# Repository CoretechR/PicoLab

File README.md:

# Pico.Lab - Web-GUI Embedded Multitool

## Overview

Pico.Lab is an open-source embedded bring-up tool built around the Raspberry Pi RP2350 microcontroller. It offers an easy-to-use, window-based web user interface directly served from on-device flash over a virtual USB Ethernet link. No host software or drivers are required - just plug it in and open your browser. The interface provides a 4-channel scope, an 8-channel logic analyzer, and an adjustable power supply with real-time monitoring. It also integrates GPIO control, a data logger, and bus masters for UART, SPI, and I2C communication.

## Features

*   **Easy to use**: A fast and intuitive window-based user interface lets you control all the integrated tools easily. It supports multitasking across its tools, windows-resizing and customization. For automation you can use the integrated CLI via the virtual COM port.
*   **No extra software or hardware needed**: The entire graphical interface is hosted on device using a lightweight web server. No WebUSB needed - It works seamlessly in any browser on any modern operating system. At only 200 KB in size, the interface fits comfortably in the Pico's RAM and loads in a fraction of a second.
*   **Integrated tools**: The firmware enables the Raspberry Pi Pico to become a multi-functional instrument for analog and digital debugging. The following tools are implemented so far:
    *   **Oscilloscope**: 4-channel analog capture with configurable timebase, voltage scaling, trigger settings, and continuous/single-shot modes. Utilizes overclocked ADC (192MHz) and DMA for high-speed continuous streaming for a bandwidth of around 400 kHz.
    *   **GPIO Control**: Directly read, write, and configure the 8 GPIO pins. Supports input/output modes, Pull-up configuration, and PWM control.
    *   **Data Logger**: Long-term, slow-rate sampling of both analog and digital pins with direct `.csv` export functionality.
    *   **Logic Analyzer**: 8-channel digital capture (D0–D7) capable of capturing at up to 100 MS/s. Features adjustable timebases, edge triggering, and Run-Length Encoding (RLE) compression for high-speed transmission. Integrated decoders for UART, I2C and SPI.
    *   **UART Terminal**: Serial bridge for interacting with target devices. Includes baud rate configuration, CR/LF ending controls, and live TX/RX logging.
    *   **Power Supply Controller**: Real-time control and monitoring of adjustable voltage/current rails (5V, 3.3V, and a fully adjustable output). Live telemetry graphing for current draw and voltage levels. Only available when using the Pico.Lab board.
    *   **I2C & SPI Masters**: Dedicated bus tools to scan for I2C devices, configure bus baud rates, and execute raw read/write transactions.

## Software

Pico.Lab is built entirely on native, lightweight frameworks to maximize the RP2350's performance.

*   **Firmware Backend (C)**:
    *   Built on the **Raspberry Pi Pico SDK**.
    *   **TinyUSB**: Provides USB CDC (Serial CLI) and RNDIS/ECM (Virtual Ethernet).
    *   **lwIP**: Handles TCP/IP, DHCP (assigning an IP to your PC), DNS (resolving `pico.lab`), and the embedded HTTP server.
    *   **Dual-Core Processing**: Core 0 handles networking, USB, and UI serving. Core 1 is dedicated entirely to high-frequency ADC/DMA sampling and logic capturing.
*   **Web Frontend (HTML/JS/CSS)**:
    *   Zero-dependency Vanilla JavaScript UI. Runs fully offline.
    *   **WinBox.js**: Used for the robust, draggable, desktop-like window manager.
    *   **Server-Sent Events (SSE)**: Pushes high-speed live telemetry data from the Pico to the browser over TCP.

## Hardware

Pico.Lab is designed to run best on the custom Pico.Lab board, but is fully compatible with standard Raspberry Pi Pico (RP2040) and Raspberry Pi Pico 2 (RP2350) boards out of the box. So if you have a Pico lying around, give the .uf2 files a try!

The Pico.Lab board adds the following features:
* Support for logic voltages from 1.65V to 5.5V
* Adjustable power rail (1-5V)
* 4x Analog Channels with 12V input range and op-amp buffer
* 8x Digital Inputs/Outputs with configurable pull-ups
* Current measurement for 5V, 3.3V, and adjustable rail
* Dedicated SPI, I2C and UART pins
* Protection against ESD, over-voltage, over-current, reverse current

## Current State of this Project

My main goal for this project was to be an easy-to-use toolkit for simple debugging applications. You want to know why an I2C sensor does not respond, what current your Wifi module is drawing or why a servo does not move? Just plug your hardware in and start debugging without checking a manual first. But since this is running on a 1$ microcontroller over a USB 1.1 link, don't expect the performance of professional instruments. The Pico will do significantly worse than any dedicated scope or logic analyzer. However, with the existing hardware there is still room for improvements, for example:
* [ ] Save/Restore tool configurations
* [ ] JTAG support
* [ ] a servo tester app

## Getting Started

### Flashing the firmware
1. Download the corresponding .uf2 file for your Rp2040 or RP2350. 
2. Put the device into BOOTSEL-Mode and drop the .uf2-File into its volume.

### Connecting to Pico.Lab
1. Connect the Pico.Lab board to your computer via USB.
2. The board will mount as a virtual network adapter. It automatically acts as a DHCP server.
3. Open your web browser and navigate to:
   * **http://pico.lab**
   * *(Alternatively, http://192.168.7.1 if your OS doesn't support local DNS).*
### Serial CLI
If you prefer a command-line interface, Pico.Lab also acts as a standard USB Serial (CDC) device. Connect via your favorite serial terminal (e.g., PuTTY) at 115200 baud.
Type `help` to see a list of commands (e.g., `gpio`, `adc`, `power`, `i2c`, `spi`, `sys`).

## Building from Source

### Prerequisites
* [Raspberry Pi Pico SDK](https://github.com/raspberrypi/pico-sdk)
* CMake & Ninja/Make
* GCC ARM Embedded Toolchain

### Build Instructions
```bash
git clone https://github.com/CoretechR/picolab.git
cd picolab
mkdir build && cd build
cmake ..
make -j$(nproc)
```
Select your type of Raspberry Pi Pico board in the Pico SDK. For the Pico.Lab board, set the PICOLAB_HW_CUSTOM_BOARD define in board_config.h. You can also use this file to modify the pins for GPIO, SPI, I2C and UART.

Flash the resulting `.uf2` file to your board by holding the `BOOTSEL` button while plugging it in, then drag-and-drop the file to the `RPI-RP2` drive.

## Disclosure about AI Usage

While I remain pessimistic about the impact of AI on humanity, there is no putting it back in the box. For this project, I tried to embrace it and used it heavily to generate the firmware, web frontend and parts of the documentation. I wanted to see what I could achieve in the same amount of time that I normally put into my hobby projects. All art, design and architecture were conceived by me. 

## License

This project is licensed under the **GPL-3.0 License** - see the [LICENSE](LICENSE) file for details.
Copyright © 2026 Maximilian Kern.

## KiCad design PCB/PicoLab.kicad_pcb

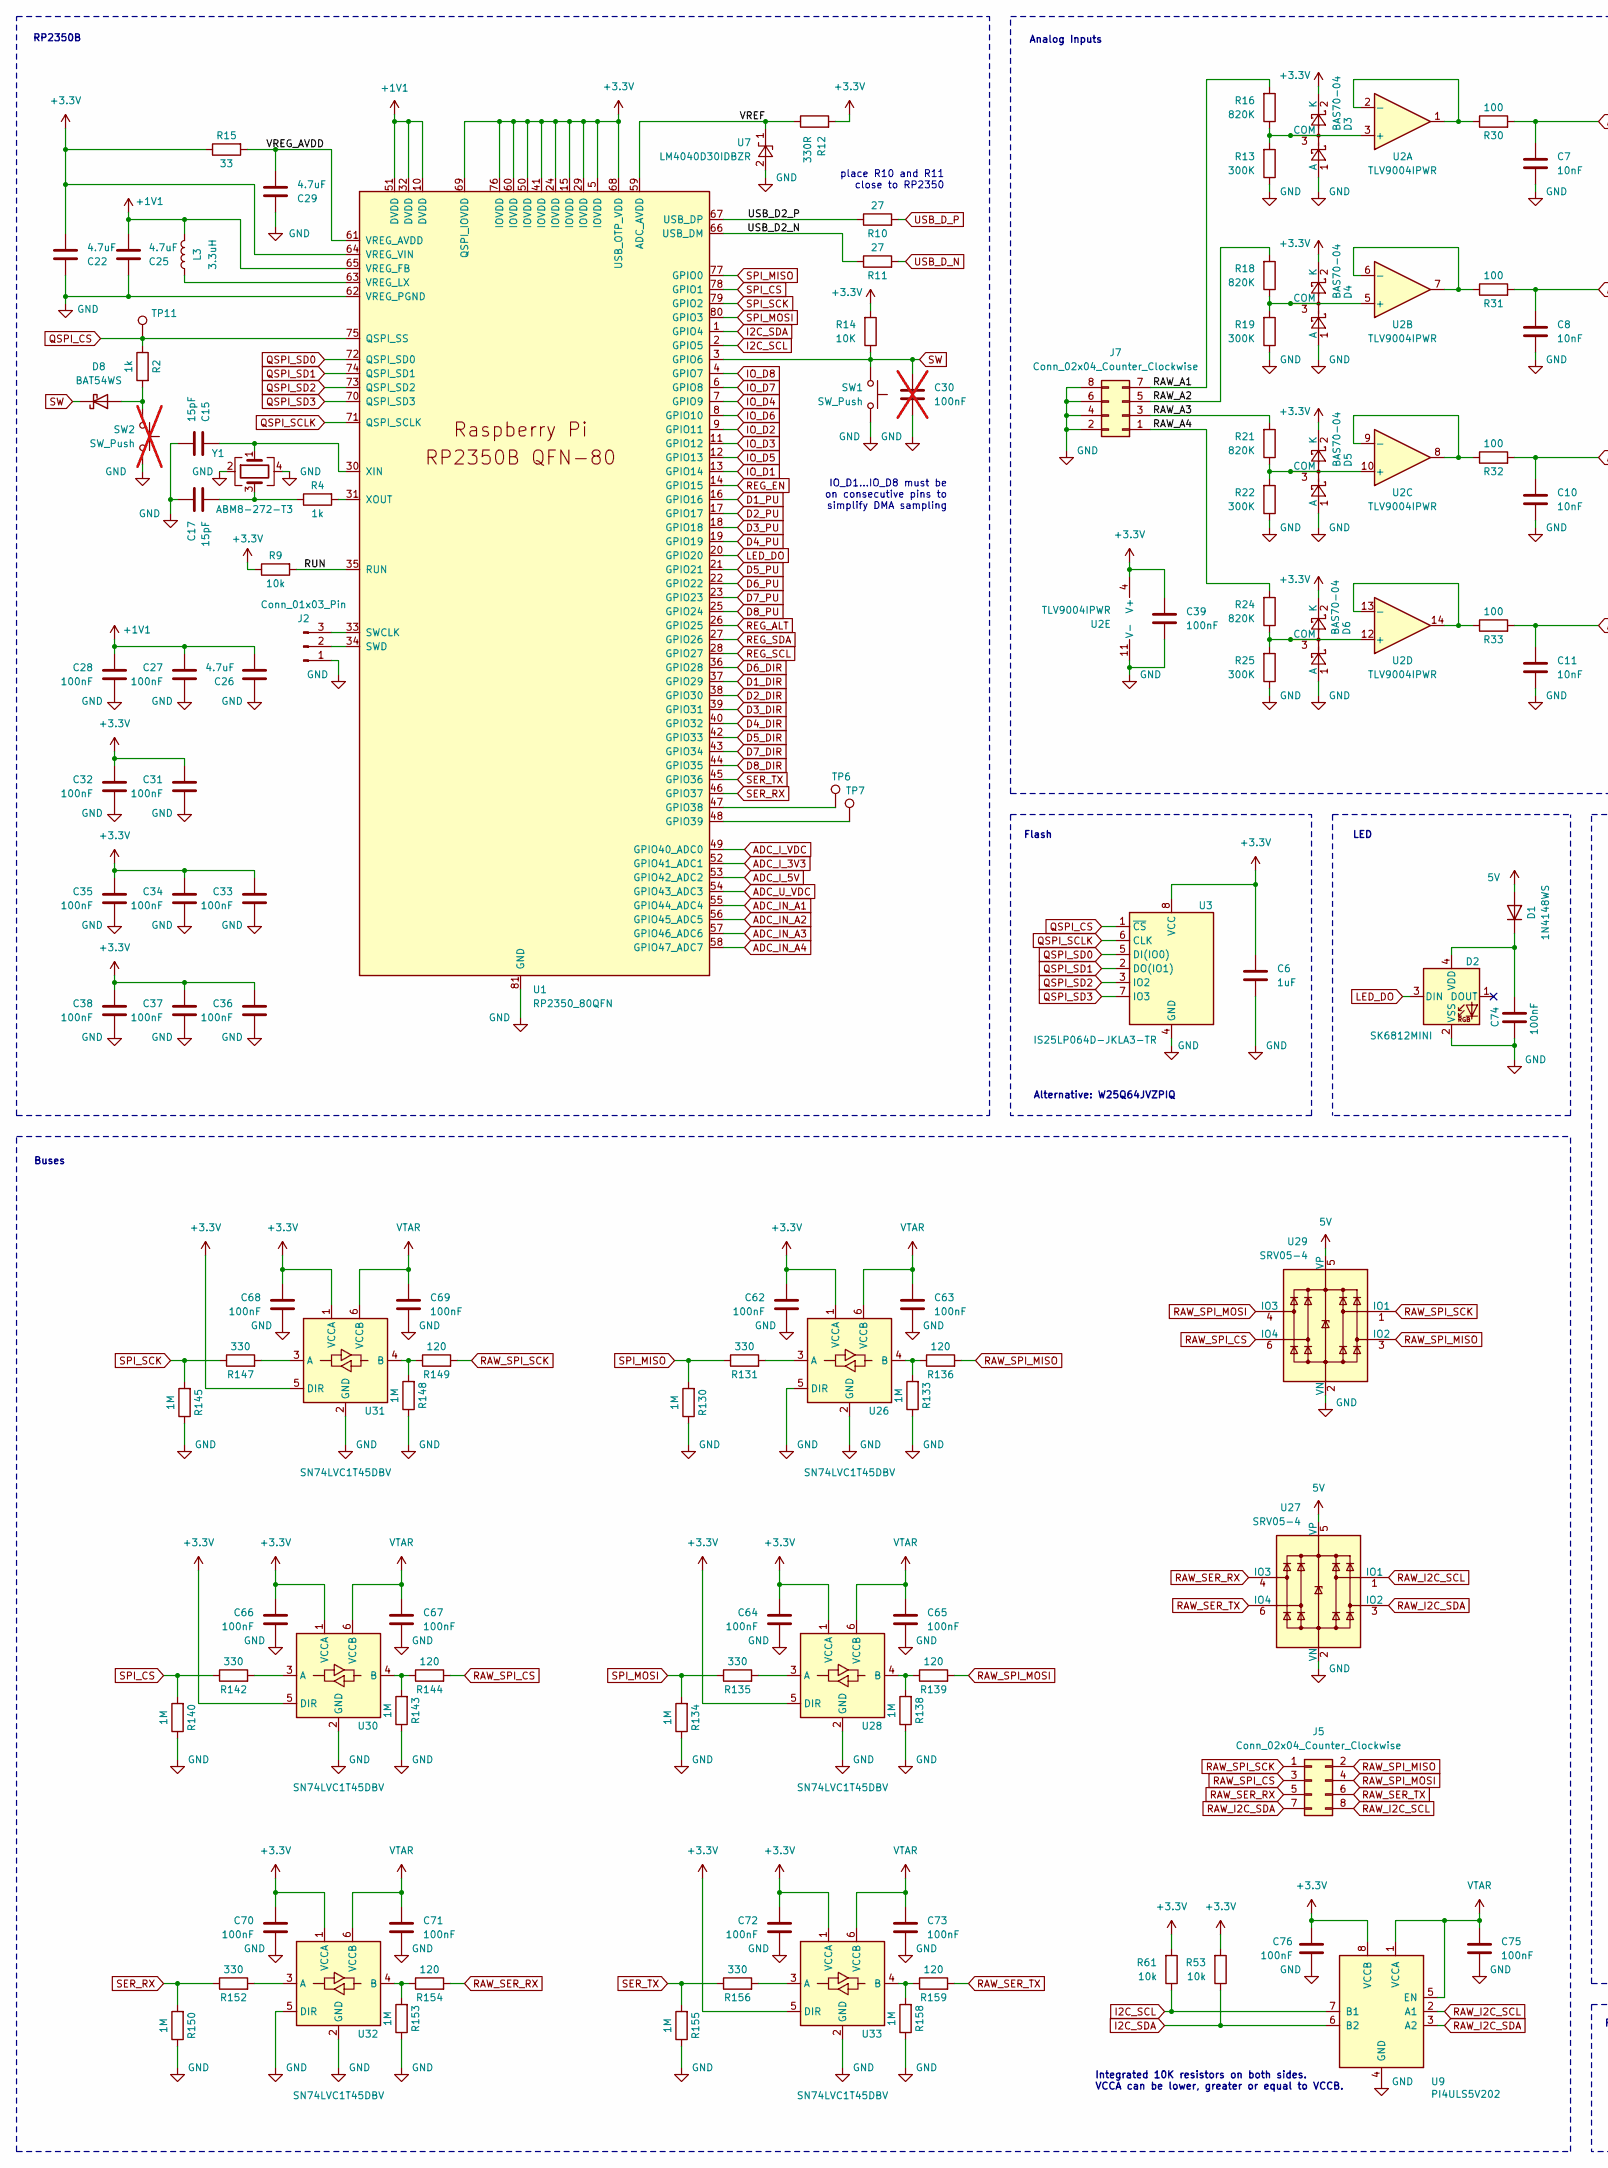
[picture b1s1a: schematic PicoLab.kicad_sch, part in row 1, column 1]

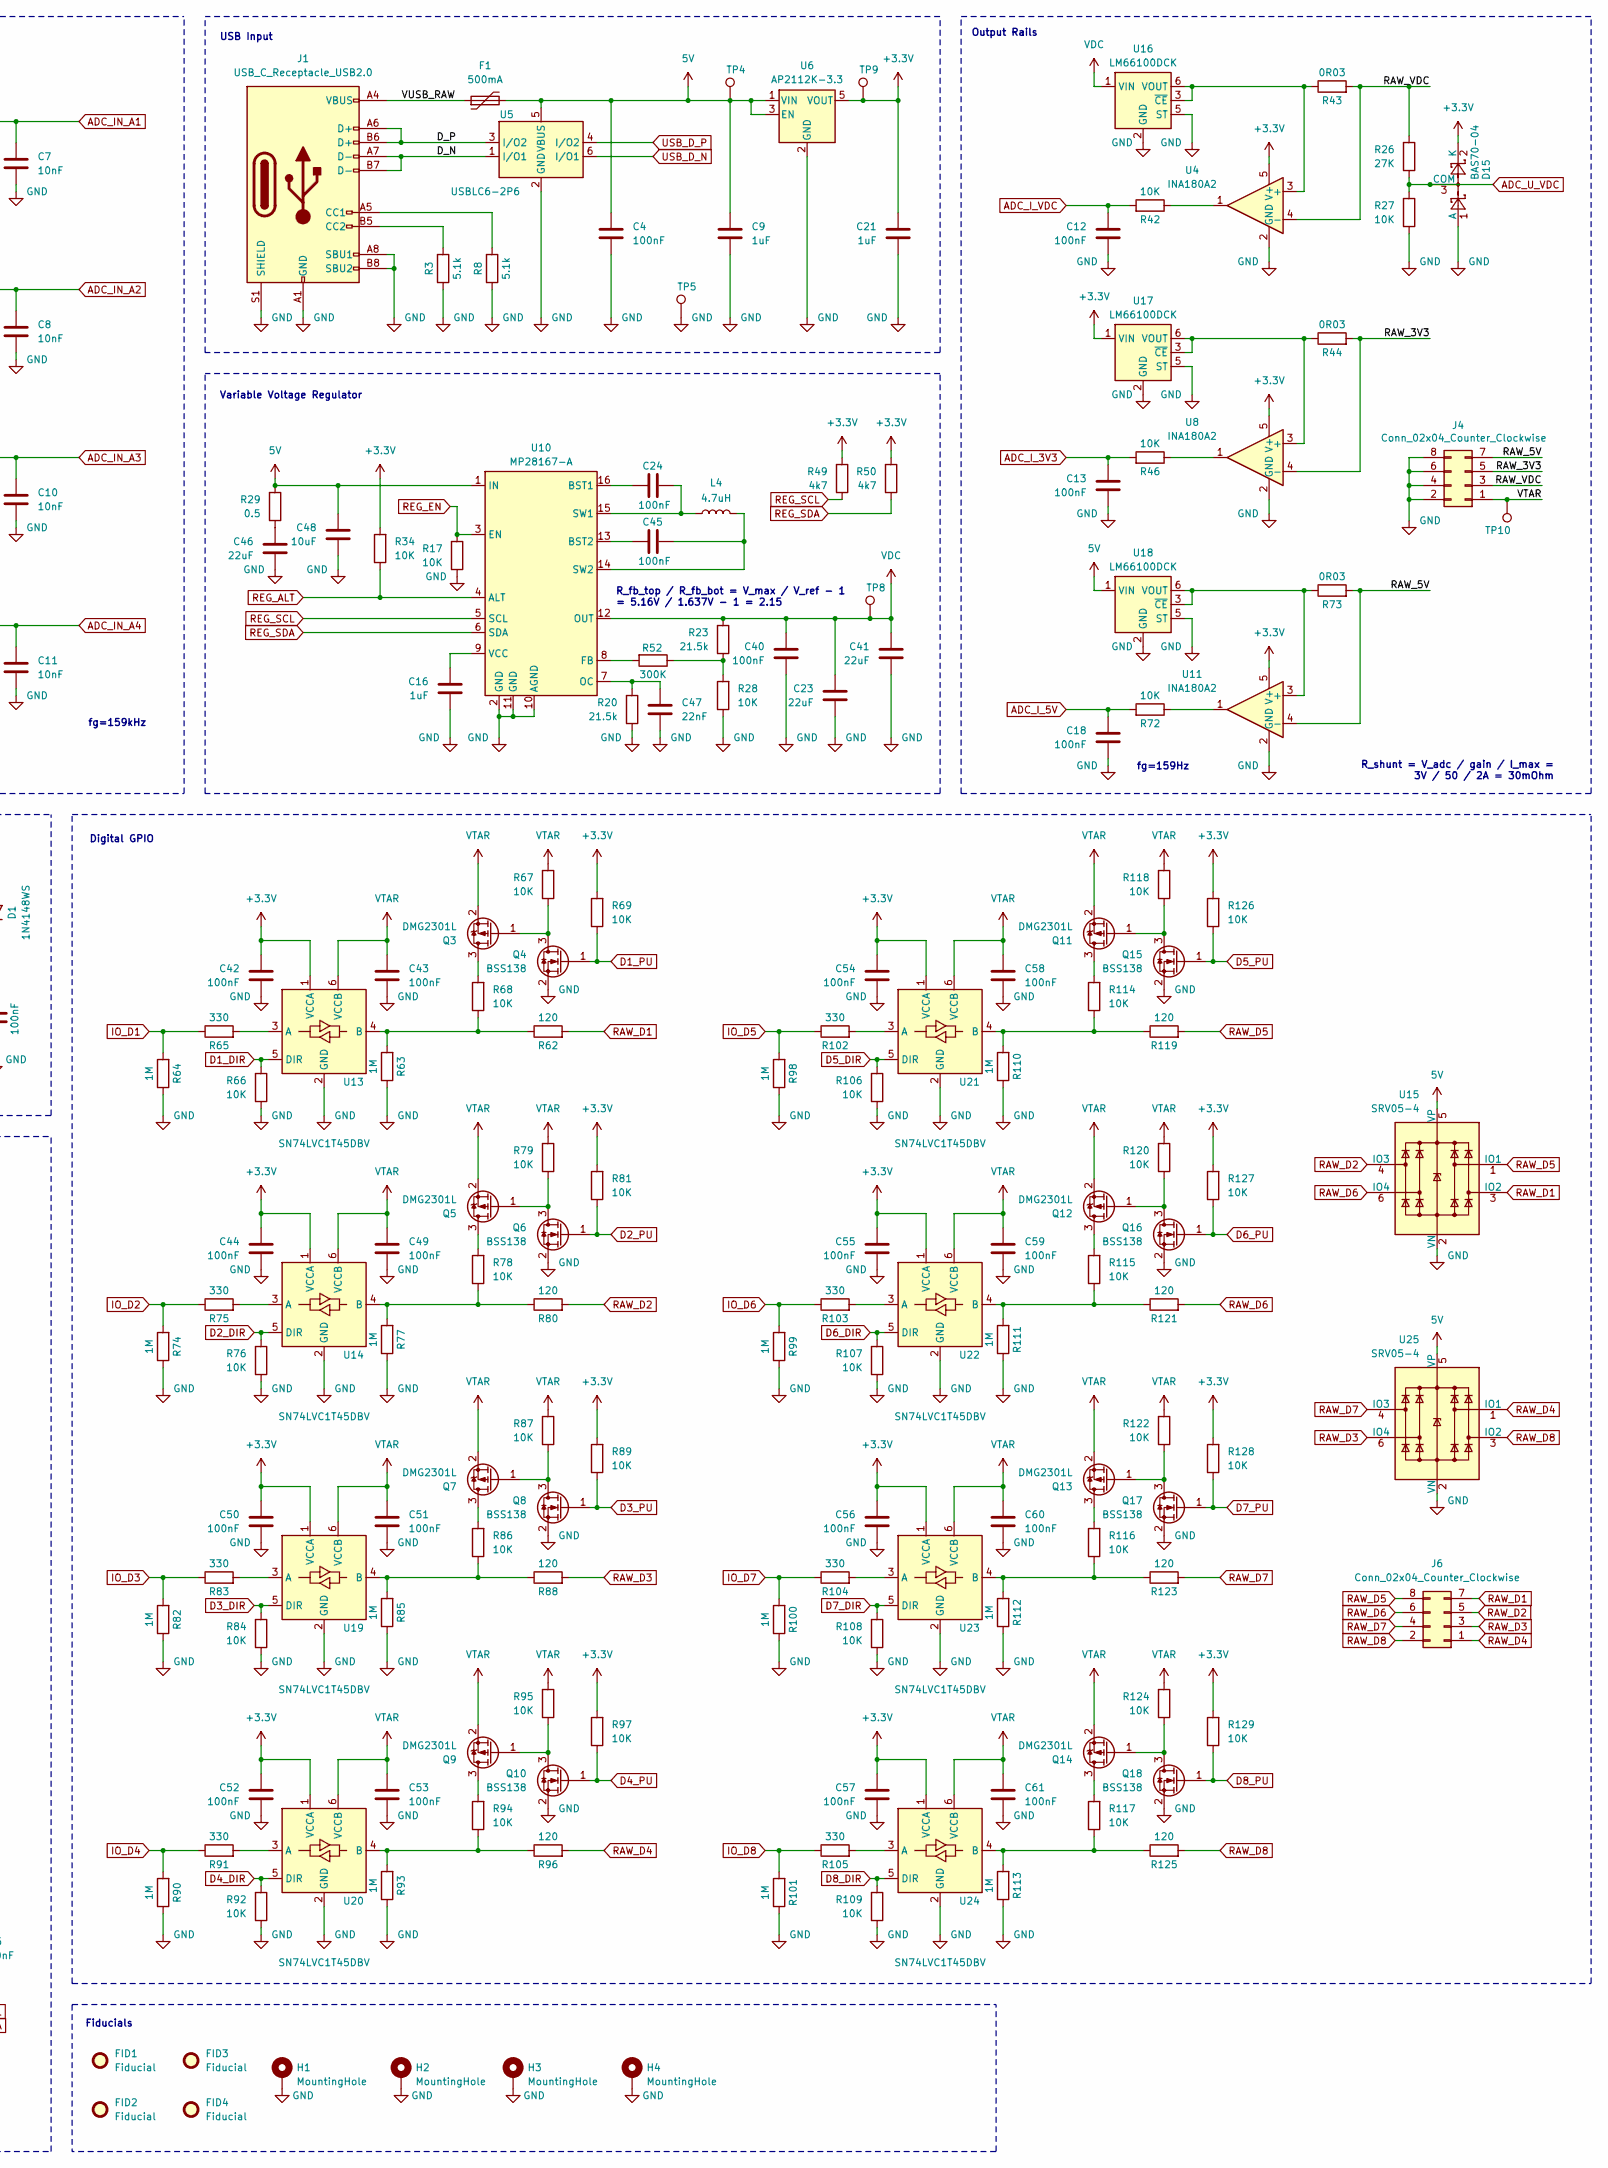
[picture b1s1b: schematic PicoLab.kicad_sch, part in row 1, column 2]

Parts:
C4, C12, C13, C18, C24, C27, C28, C31, C32, C33, C34, C35, C36, C37, C38, C39, C40, C42, C43, C44, C45, C49, C50, C51, C52, C53, C54, C55, C56, C57, C58, C59, C60, C61, C62, C63, C64, C65, C66, C67, C68, C69, C70, C71, C72, C73, C74, C75, C76: 100nF; C_0603_1608Metric; LCSC C1591
C6, C9, C16, C21: 1uF; C_0603_1608Metric; LCSC C15849
C7, C8, C10, C11: 10nF; C_0603_1608Metric
C15, C17: 15pF; C_0603_1608Metric; LCSC C107037
C22, C25, C26, C29: 4.7uF; C_0603_1608Metric; LCSC C1705
C23, C41: 22uF; C_1206_3216Metric; LCSC C91604
C30: 100nF; C_0603_1608Metric; LCSC C1591; not fitted
C46: 22uF; C_1206_3216Metric
C47: 22nF; C_0603_1608Metric; LCSC C106222
C48: 10uF; C_0805_2012Metric
D1: 1N4148WS; D_SOD-323; LCSC C118873
D2: SK6812MINI; LED_SK6812MINI_PLCC4_3.5x3.5mm_P1.75mm; LCSC C2886570
D3, D4, D5, D6: BAS70-04; SOT-23; LCSC C54194934
D8: BAT54WS; D_SOD-323; LCSC C124205
D15: BAS70-04; SOT-23
F1: 500mA; Fuse_1206_3216Metric_Pad1.42x1.75mm_HandSolder; LCSC C220146
FID1, FID2, FID3, FID4: Fiducial; Fiducial_1mm_Mask2mm
H1, H2, H3, H4: MountingHole; MountingHole_3.2mm_M3_Pad_Via
J1: USB_C_Receptacle_USB2.0; USB_C_Receptacle_HRO_TYPE-C-31-M-12; LCSC C2982555
J2: Conn_01x03_Pin; JST_SH_SM03B-SRSS-TB_1x03-1MP_P1.00mm_Horizontal; LCSC C160403
J4, J5, J6, J7: Conn_02x04_Counter_Clockwise; 10129382-908003BLF; LCSC C6970143
L3: 3.3uH; L_pol_2016; LCSC C42411119
L4: 4.7uH; L_1008_2520Metric; LCSC C668313
Q3, Q5, Q7, Q9, Q11, Q12, Q13, Q14: DMG2301L; SOT-23; LCSC C7472914
Q4, Q6, Q8, Q10, Q15, Q16, Q17, Q18: BSS138; SOT-23; LCSC C52895
R2, R4: 1k; R_0603_1608Metric; LCSC C22548
R3, R8: 5.1k; R_0603_1608Metric; LCSC C105580
R9, R53, R61: 10k; R_0603_1608Metric; LCSC C98220
R10, R11: 27; R_0603_1608Metric; LCSC C137753
R12: 330R; R_0603_1608Metric; LCSC C105881
R13, R19, R22, R25: 300K; R_0603_1608Metric
R14, R17, R27, R28, R34, R42, R46, R66, R67, R68, R69, R72, R76, R78, R79, R81, R84, R86, R87, R89, R92, R94, R95, R97, R106, R107, R108, R109, R114, R115, R116, R117, R118, R120, R122, R124, R126, R127, R128, R129: 10K; R_0603_1608Metric; LCSC C98220
R15: 33; R_0603_1608Metric
R16, R18, R21, R24: 820K; R_0603_1608Metric
R20, R23: 21.5k; R_0603_1608Metric
R26: 27K; R_0603_1608Metric
R29: 0.5; R_0603_1608Metric
R30, R31, R32, R33: 100; R_0603_1608Metric; LCSC C125923
R43, R44, R73: 0R03; R_0603_1608Metric; LCSC C422943
R49, R50: 4k7; R_0603_1608Metric; LCSC C99782
R52: 300K; R_0603_1608Metric; LCSC C116699
R62, R80, R88, R96, R119, R121, R123, R125, R136, R139, R144, R149, R154, R159: 120; R_0603_1608Metric; LCSC C125925
R63, R64, R74, R77, R82, R85, R90, R93, R98, R99, R100, R101, R110, R111, R112, R113, R130, R133, R134, R138, R140, R143, R145, R148, R150, R153, R155, R158: 1M; R_0603_1608Metric; LCSC C217860
R65, R75, R83, R91, R102, R103, R104, R105, R131, R135, R142, R147, R152, R156: 330; R_0603_1608Metric
SW1: SW_Push; Panasonic_EVQPUM_EVQPUD; LCSC C388642
SW2: SW_Push; SW_SPST_EVQP2_ShortPushTravel_H2.1mm; LCSC C2915174; not fitted
TP4, TP5, TP6, TP7, TP8, TP9, TP10, TP11: TestPoint; TestPoint_Pad_D1.5mm
U1: RP2350_80QFN; QFN-80-1EP_10x10mm_P0.4mm_EP3.4x3.4mm
U2: TLV9004IPWR; TSSOP-14_4.4x5mm_P0.65mm; LCSC C2058050
U3: IS25LP064D-JKLA3-TR; WSON-8-1EP_6x5mm_P1.27mm_EP3.4x4.3mm; LCSC C27531352
U4, U8, U11: INA180A2; SOT-23-5; LCSC C192764
U5: USBLC6-2P6; SOT-666; LCSC C2827693
U6: AP2112K-3.3; SOT-23-5; LCSC C51118
U7: LM4040D30IDBZR; SOT-23; LCSC C130178
U9: PI4ULS5V202; MSOP-8_3x3mm_P0.65mm; LCSC C481697
U10: MP28167-A; QFN-16_3x3mm_P0.5mm_MPS
U13, U14, U19, U20, U21, U22, U23, U24, U26, U28, U30, U31, U32, U33: SN74LVC1T45DBV; SOT-23-6; LCSC C7843
U15, U25, U27, U29: SRV05-4; SOT-23-6; LCSC C558418
U16, U17, U18: LM66100DCK; SOT-363_SC-70-6; LCSC C2869734
Y1: ABM8-272-T3; Crystal_SMD_Abracon_ABM8G-4Pin_3.2x2.5mm; LCSC C20625731

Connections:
5V: C4.1, C9.1, C48.1, D1.2 (A), F1.2, R29.2, TP4.1 (1_1), U5.5 (VBUS), U6.1 (VIN), U6.3 (EN), U10.1 (IN), U15.5 (VP), U18.1 (VIN), U25.5 (VP), U27.5 (VP), U29.5 (VP)
+1V1: C25.2, C26.2, C27.1, C28.1, L3.1, U1.10 (DVDD), U1.32 (DVDD), U1.51 (DVDD), U1.65 (VREG_FB)
+3.3V: C6.1, C21.1, C22.2, C31.1, C32.1, C33.1, C34.1, C35.1, C36.1, C37.1, C38.1, C39.1, C42.1, C44.1, C50.1, C52.1, C54.1, C55.1, C56.1, C57.1, C62.1, C64.1, C66.1, C68.1, C70.1, C72.1, C76.1, D3.2 (K), D4.2 (K), D5.2 (K), D6.2 (K), D15.2 (K), R9.1, R12.2, R14.2, R15.1, R34.2, R49.2, R50.2, R53.2, R61.2, R69.2, R81.2, R89.2, R97.2, R126.2, R127.2, R128.2, R129.2, TP9.1 (1_1), U1.5 (IOVDD), U1.15 (IOVDD), U1.24 (IOVDD), U1.29 (IOVDD), U1.41 (IOVDD), U1.50 (IOVDD), U1.60 (IOVDD), U1.64 (VREG_VIN), U1.68 (USB_OTP_VDD), U1.69 (QSPI_IOVDD), U1.76 (IOVDD), U2.4 (V+), U3.8 (VCC), U4.5 (V+), U6.5 (VOUT), U8.5 (V+), U9.8 (VCCB), U11.5 (V+), U13.1 (VCCA), U14.1 (VCCA), U17.1 (VIN), U19.1 (VCCA), U20.1 (VCCA), U21.1 (VCCA), U22.1 (VCCA), U23.1 (VCCA), U24.1 (VCCA), U26.1 (VCCA), U28.1 (VCCA), U28.5 (DIR), U30.1 (VCCA), U30.5 (DIR), U31.1 (VCCA), U31.5 (DIR), U32.1 (VCCA), U33.1 (VCCA), U33.5 (DIR)
/D_N: J1.A7 (D-), J1.B7 (D-), U5.1 (I/O1)
/D_P: J1.A6 (D+), J1.B6 (D+), U5.3 (I/O2)
/RAW_3V3: J4.5, R44.2, U8.4 (-)
/RAW_5V: J4.7, R73.2, U11.4 (-)
/RAW_A1: J7.7, R16.2
/RAW_A2: J7.5, R18.2
/RAW_A3: J7.3, R21.2
/RAW_A4: J7.1, R24.2
/RAW_VDC: J4.3, R26.2, R43.2, U4.4 (-)
/RUN: R9.2, U1.35 (RUN)
/USB_D2_N: R11.1, U1.66 (USB_DM)
/USB_D2_P: R10.1, U1.67 (USB_DP)
/VREF: R12.1, U1.59 (ADC_AVDD), U7.1 (K)
/VREG_AVDD: C29.2, R15.2, U1.61 (VREG_AVDD)
/VUSB_RAW: F1.1, J1.A4 (VBUS), J1.A9 (VBUS), J1.B4 (VBUS), J1.B9 (VBUS)
ADC_IN_A1: C7.1, R30.2, U1.55 (GPIO44_ADC4)
ADC_IN_A2: C8.1, R31.2, U1.56 (GPIO45_ADC5)
ADC_IN_A3: C10.1, R32.2, U1.57 (GPIO46_ADC6)
ADC_IN_A4: C11.1, R33.2, U1.58 (GPIO47_ADC7)
ADC_I_3V3: C13.1, R46.2, U1.52 (GPIO41_ADC1)
ADC_I_5V: C18.1, R72.2, U1.53 (GPIO42_ADC2)
ADC_I_VDC: C12.1, R42.2, U1.49 (GPIO40_ADC0)
ADC_U_VDC: D15.3 (COM), R26.1, R27.2, U1.54 (GPIO43_ADC3)
D1_DIR: R66.2, U1.37 (GPIO29), U13.5 (DIR)
D1_PU: Q4.1 (G), R69.1, U1.16 (GPIO16)
D2_DIR: R76.2, U1.38 (GPIO30), U14.5 (DIR)
D2_PU: Q6.1 (G), R81.1, U1.17 (GPIO17)
D3_DIR: R84.2, U1.39 (GPIO31), U19.5 (DIR)
D3_PU: Q8.1 (G), R89.1, U1.18 (GPIO18)
D4_DIR: R92.2, U1.40 (GPIO32), U20.5 (DIR)
D4_PU: Q10.1 (G), R97.1, U1.19 (GPIO19)
D5_DIR: R106.2, U1.42 (GPIO33), U21.5 (DIR)
D5_PU: Q15.1 (G), R126.1, U1.21 (GPIO21)
D6_DIR: R107.2, U1.36 (GPIO28), U22.5 (DIR)
D6_PU: Q16.1 (G), R127.1, U1.22 (GPIO22)
D7_DIR: R108.2, U1.43 (GPIO34), U23.5 (DIR)
D7_PU: Q17.1 (G), R128.1, U1.23 (GPIO23)
D8_DIR: R109.2, U1.44 (GPIO35), U24.5 (DIR)
D8_PU: Q18.1 (G), R129.1, U1.25 (GPIO24)
GND: C4.2, C6.2, C7.2, C8.2, C9.2, C10.2, C11.2, C12.2, C13.2, C15.2, C16.2, C17.1, C18.2, C21.2, C22.1, C23.2, C25.1, C26.1, C27.2, C28.2, C29.1, C30.2, C31.2, C32.2, C33.2, C34.2, C35.2, C36.2, C37.2, C38.2, C39.2, C40.2, C41.2, C42.2, C43.2, C44.2, C46.2, C47.2, C48.2, C49.2, C50.2, C51.2, C52.2, C53.2, C54.2, C55.2, C56.2, C57.2, C58.2, C59.2, C60.2, C61.2, C62.2, C63.2, C64.2, C65.2, C66.2, C67.2, C68.2, C69.2, C70.2, C71.2, C72.2, C73.2, C74.1, C75.2, C76.2, D2.2 (VSS), D3.1 (A), D4.1 (A), D5.1 (A), D6.1 (A), D15.1 (A), H1.1 (1_1), H2.1 (1_1), H3.1 (1_1), H4.1 (1_1), J1.A1 (GND), J1.A8 (SBU1), J1.A12 (GND), J1.B1 (GND), J1.B8 (SBU2), J1.B12 (GND), J1.S1 (SHIELD), J2.1, J4.2, J4.4, J4.6, J4.8, J7.2, J7.4, J7.6, J7.8, Q4.2 (S), Q6.2 (S), Q8.2 (S), Q10.2 (S), Q15.2 (S), Q16.2 (S), Q17.2 (S), Q18.2 (S), R3.1, R8.1, R13.1, R17.1, R19.1, R20.1, R22.1, R25.1, R27.1, R28.1, R63.1, R64.1, R66.1, R74.1, R76.1, R77.1, R82.1, R84.1, R85.1, R90.1, R92.1, R93.1, R98.1, R99.1, R100.1, R101.1, R106.1, R107.1, R108.1, R109.1, R110.1, R111.1, R112.1, R113.1, R130.1, R133.1, R134.1, R138.1, R140.1, R143.1, R145.1, R148.1, R150.1, R153.1, R155.1, R158.1, SW1.1, SW2.1, TP5.1 (1_1), U1.62 (VREG_PGND), U1.81 (GND), U2.11 (V-), U3.4 (GND), U4.2 (GND), U5.2 (GND), U6.2 (GND), U7.2 (A), U8.2 (GND), U9.4 (GND), U10.2 (GND), U10.10 (AGND), U10.11 (GND), U11.2 (GND), U13.2 (GND), U14.2 (GND), U15.2 (VN), U16.2 (GND), U16.5 (ST), U17.2 (GND), U17.5 (ST), U18.2 (GND), U18.5 (ST), U19.2 (GND), U20.2 (GND), U21.2 (GND), U22.2 (GND), U23.2 (GND), U24.2 (GND), U25.2 (VN), U26.2 (GND), U26.5 (DIR), U27.2 (VN), U28.2 (GND), U29.2 (VN), U30.2 (GND), U31.2 (GND), U32.2 (GND), U32.5 (DIR), U33.2 (GND), Y1.2, Y1.4
I2C_SCL: R61.1, U1.2 (GPIO5), U9.7 (B1)
I2C_SDA: R53.1, U1.1 (GPIO4), U9.6 (B2)
IO_D1: R64.2, R65.1, U1.13 (GPIO14)
IO_D2: R74.2, R75.1, U1.9 (GPIO11)
IO_D3: R82.2, R83.1, U1.11 (GPIO12)
IO_D4: R90.2, R91.1, U1.7 (GPIO9)
IO_D5: R98.2, R102.1, U1.12 (GPIO13)
IO_D6: R99.2, R103.1, U1.8 (GPIO10)
IO_D7: R100.2, R104.1, U1.6 (GPIO8)
IO_D8: R101.2, R105.1, U1.4 (GPIO7)
LED_DO: D2.3 (DIN), U1.20 (GPIO20)
unnamed: C17.2, R4.1, Y1.3
unnamed: C46.1, R29.1
unnamed: C74.2, D1.1 (K), D2.4 (VDD)
unnamed: D3.3 (COM), R13.2, R16.1, U2.3 (+)
unnamed: D4.3 (COM), R18.1, R19.2, U2.5 (+)
unnamed: D5.3 (COM), R21.1, R22.2, U2.10 (+)
unnamed: D6.3 (COM), R24.1, R25.2, U2.12 (+)
unnamed: D8.2 (A), R2.2, SW2.2
unnamed: J1.A5 (CC1), R8.2
unnamed: J1.B5 (CC2), R3.2
unnamed: J2.2, U1.34 (SWD)
unnamed: J2.3, U1.33 (SWCLK)
unnamed: Q3.3 (D), R68.2
unnamed: Q3.1 (G), Q4.3 (D), R67.1
unnamed: Q5.3 (D), R78.2
unnamed: Q5.1 (G), Q6.3 (D), R79.1
unnamed: Q7.3 (D), R86.2
unnamed: Q7.1 (G), Q8.3 (D), R87.1
unnamed: Q9.3 (D), R94.2
unnamed: Q9.1 (G), Q10.3 (D), R95.1
unnamed: Q11.3 (D), R114.2
unnamed: Q11.1 (G), Q15.3 (D), R118.1
unnamed: Q12.3 (D), R115.2
unnamed: Q12.1 (G), Q16.3 (D), R120.1
unnamed: Q13.3 (D), R116.2
unnamed: Q13.1 (G), Q17.3 (D), R122.1
unnamed: Q14.3 (D), R117.2
unnamed: Q14.1 (G), Q18.3 (D), R124.1
unnamed: R23.1, R28.2, R52.1
unnamed: R42.1, U4.1
unnamed: R46.1, U8.1
unnamed: R72.1, U11.1
unnamed: TP6.1 (1_1), U1.47 (GPIO38)
unnamed: TP7.1 (1_1), U1.48 (GPIO39)
unnamed: L3.2, U1.63 (VREG_LX)
unnamed: C15.1, U1.30 (XIN), Y1.1
unnamed: R4.2, U1.31 (XOUT)
unnamed: R30.1, U2.1, U2.2 (-)
unnamed: R31.1, U2.6 (-), U2.7
unnamed: R32.1, U2.8, U2.9 (-)
unnamed: R33.1, U2.13 (-), U2.14
unnamed: C24.2, U10.16 (BST1)
unnamed: C45.2, U10.13 (BST2)
unnamed: R52.2, U10.8 (FB)
unnamed: C47.1, R20.2, U10.7 (OC)
unnamed: C24.1, L4.2, U10.15 (SW1)
unnamed: C45.1, L4.1, U10.14 (SW2)
unnamed: C16.1, U10.9 (VCC)
unnamed: R73.1, U11.3 (+), U18.3 (~CE), U18.6 (VOUT)
unnamed: R65.2, U13.3 (A)
unnamed: R62.1, R63.2, R68.1, U13.4 (B)
unnamed: R75.2, U14.3 (A)
unnamed: R77.2, R78.1, R80.1, U14.4 (B)
unnamed: R43.1, U4.3 (+), U16.3 (~CE), U16.6 (VOUT)
unnamed: R44.1, U8.3 (+), U17.3 (~CE), U17.6 (VOUT)
unnamed: R83.2, U19.3 (A)
unnamed: R85.2, R86.1, R88.1, U19.4 (B)
unnamed: R91.2, U20.3 (A)
unnamed: R93.2, R94.1, R96.1, U20.4 (B)
unnamed: R102.2, U21.3 (A)
unnamed: R110.2, R114.1, R119.1, U21.4 (B)
unnamed: R103.2, U22.3 (A)
unnamed: R111.2, R115.1, R121.1, U22.4 (B)
unnamed: R104.2, U23.3 (A)
unnamed: R112.2, R116.1, R123.1, U23.4 (B)
unnamed: R105.2, U24.3 (A)
unnamed: R113.2, R117.1, R125.1, U24.4 (B)
unnamed: R131.2, U26.3 (A)
unnamed: R133.2, R136.1, U26.4 (B)
unnamed: R135.2, U28.3 (A)
unnamed: R138.2, R139.1, U28.4 (B)
unnamed: R142.2, U30.3 (A)
unnamed: R143.2, R144.1, U30.4 (B)
unnamed: R147.2, U31.3 (A)
unnamed: R148.2, R149.1, U31.4 (B)
unnamed: R152.2, U32.3 (A)
unnamed: R153.2, R154.1, U32.4 (B)
unnamed: R156.2, U33.3 (A)
unnamed: R158.2, R159.1, U33.4 (B)
QSPI_CS: R2.1, TP11.1 (1_1), U1.75 (QSPI_SS), U3.1 (~CS)
QSPI_SCLK: U1.71 (QSPI_SCLK), U3.6 (CLK)
QSPI_SD0: U1.72 (QSPI_SD0), U3.5 (DI(IO0))
QSPI_SD1: U1.74 (QSPI_SD1), U3.2 (DO(IO1))
QSPI_SD2: U1.73 (QSPI_SD2), U3.3 (IO2)
QSPI_SD3: U1.70 (QSPI_SD3), U3.7 (IO3)
RAW_D1: J6.7, R62.2, U15.3 (IO2)
RAW_D2: J6.5, R80.2, U15.4 (IO3)
RAW_D3: J6.3, R88.2, U25.6 (IO4)
RAW_D4: J6.1, R96.2, U25.1 (IO1)
RAW_D5: J6.8, R119.2, U15.1 (IO1)
RAW_D6: J6.6, R121.2, U15.6 (IO4)
RAW_D7: J6.4, R123.2, U25.4 (IO3)
RAW_D8: J6.2, R125.2, U25.3 (IO2)
RAW_I2C_SCL: J5.8, U9.2 (A1), U27.1 (IO1)
RAW_I2C_SDA: J5.7, U9.3 (A2), U27.3 (IO2)
RAW_SER_RX: J5.5, R154.2, U27.4 (IO3)
RAW_SER_TX: J5.6, R159.2, U27.6 (IO4)
RAW_SPI_CS: J5.3, R144.2, U29.6 (IO4)
RAW_SPI_MISO: J5.2, R136.2, U29.3 (IO2)
RAW_SPI_MOSI: J5.4, R139.2, U29.4 (IO3)
RAW_SPI_SCK: J5.1, R149.2, U29.1 (IO1)
REG_ALT: R34.1, U1.26 (GPIO25), U10.4 (ALT)
REG_EN: R17.2, U1.14 (GPIO15), U10.3 (EN)
REG_SCL: R49.1, U1.28 (GPIO27), U10.5 (SCL)
REG_SDA: R50.1, U1.27 (GPIO26), U10.6 (SDA)
SER_RX: R150.2, R152.1, U1.46 (GPIO37)
SER_TX: R155.2, R156.1, U1.45 (GPIO36)
SPI_CS: R140.2, R142.1, U1.78 (GPIO1)
SPI_MISO: R130.2, R131.1, U1.77 (GPIO0)
SPI_MOSI: R134.2, R135.1, U1.80 (GPIO3)
SPI_SCK: R145.2, R147.1, U1.79 (GPIO2)
SW: C30.1, D8.1 (K), R14.1, SW1.2, U1.3 (GPIO6)
USB_D_N: R11.2, U5.6 (I/O1)
USB_D_P: R10.2, U5.4 (I/O2)
VDC: C23.1, C40.1, C41.1, R23.2, TP8.1 (1_1), U10.12 (OUT), U16.1 (VIN)
VTAR: C43.1, C49.1, C51.1, C53.1, C58.1, C59.1, C60.1, C61.1, C63.1, C65.1, C67.1, C69.1, C71.1, C73.1, C75.1, J4.1, Q3.2 (S), Q5.2 (S), Q7.2 (S), Q9.2 (S), Q11.2 (S), Q12.2 (S), Q13.2 (S), Q14.2 (S), R67.2, R79.2, R87.2, R95.2, R118.2, R120.2, R122.2, R124.2, TP10.1 (1_1), U9.1 (VCCA), U9.5 (EN), U13.6 (VCCB), U14.6 (VCCB), U19.6 (VCCB), U20.6 (VCCB), U21.6 (VCCB), U22.6 (VCCB), U23.6 (VCCB), U24.6 (VCCB), U26.6 (VCCB), U28.6 (VCCB), U30.6 (VCCB), U31.6 (VCCB), U32.6 (VCCB), U33.6 (VCCB)

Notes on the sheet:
RP2350B
place R10 and R11 close to RP2350
Variable Voltage Regulator
R_shunt = V_adc / gain / I_max = 3V / 50 / 2A = 30mOhm
Alternative: W25Q64JVZPIQ
R_fb_top / R_fb_bot = V_max / V_ref - 1 = 5.16V / 1.637V - 1 = 2.15
Flash
Analog Inputs
fg=159Hz
fg=159kHz
Buses
Output Rails
LED
Digital GPIO
Fiducials
Integrated 10K resistors on both sides. VCCA can be lower, greater or equal to VCCB.
IO_D1...IO_D8 must be on consecutive pins to simplify DMA sampling
USB Input

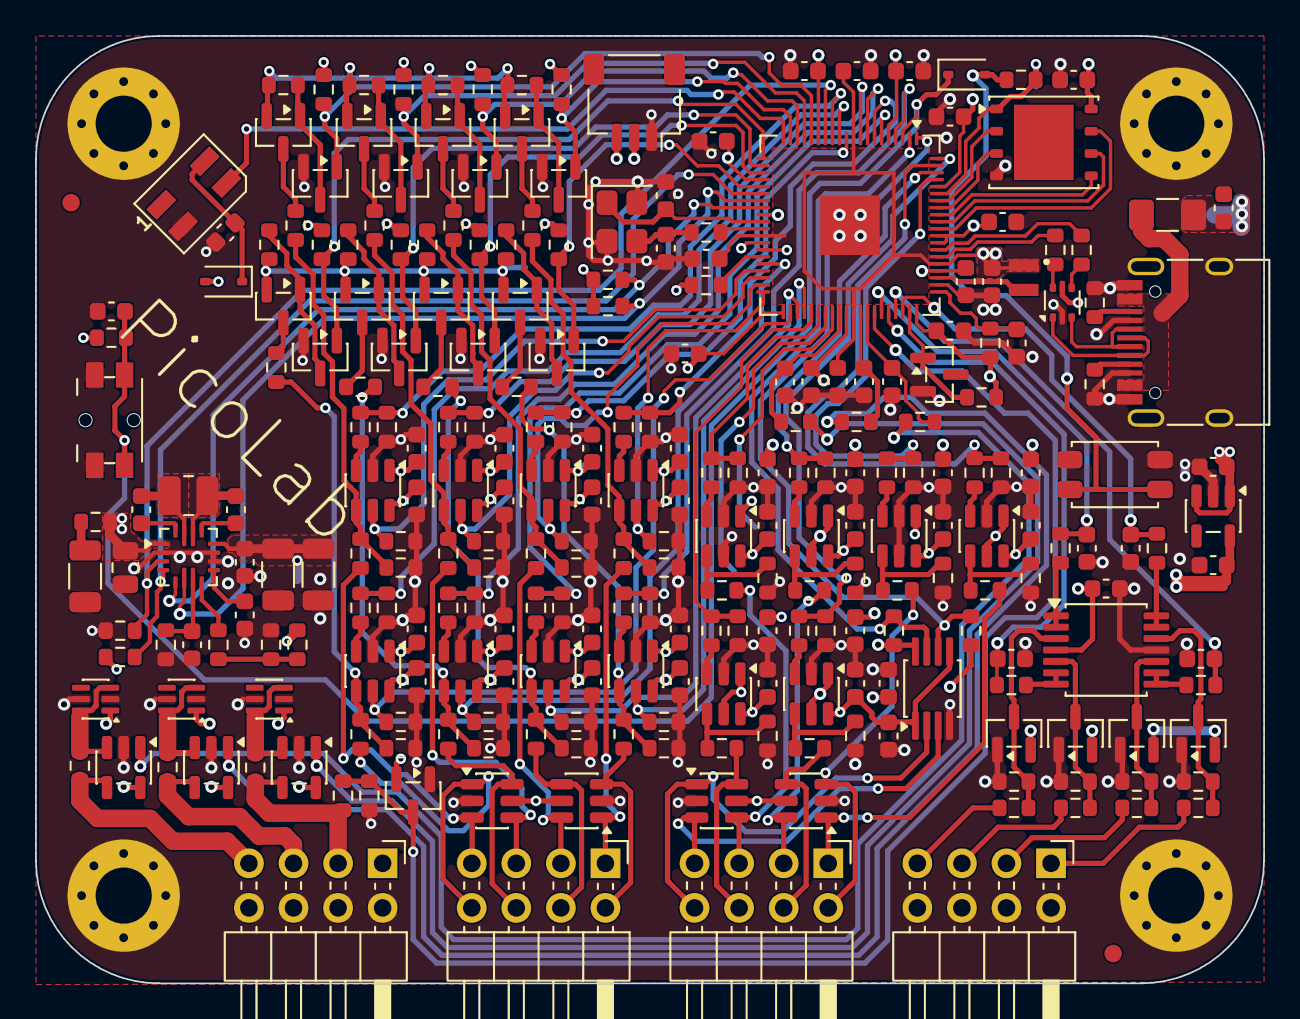
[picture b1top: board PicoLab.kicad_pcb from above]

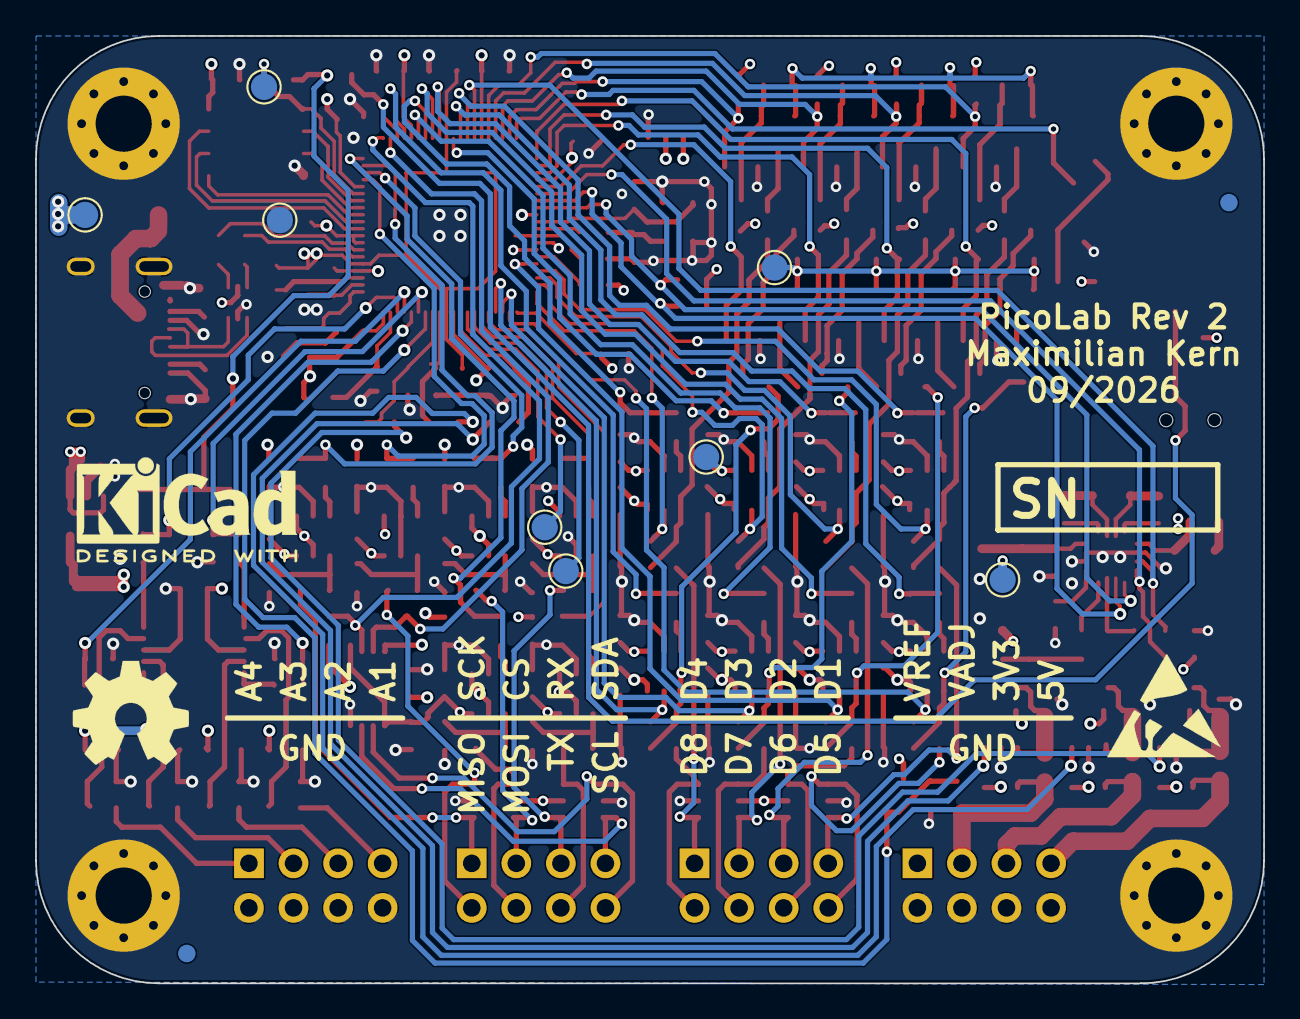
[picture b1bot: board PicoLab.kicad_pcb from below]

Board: 4 copper layers, 70.0 x 54.0 mm, 282 parts (10 on the bottom side), 170 nets.

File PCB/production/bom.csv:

Designator,Footprint,Quantity,Value,LCSC Part #
"C10, C11, C7, C8",0603,4,10nF,
"C12, C13, C18, C24, C27, C28, C31, C32, C33, C34, C35, C36, C37, C38, C39, C4, C40, C42, C43, C44, C45, C49, C50, C51, C52, C53, C54, C55, C56, C57, C58, C59, C60, C61, C62, C63, C64, C65, C66, C67, C68, C69, C70, C71, C72, C73, C74, C75, C76",0603,49,100nF,C1591
"C15, C17",0603,2,15pF,C107037
"C16, C21, C6, C9",0603,4,1uF,C15849
"C22, C25, C26, C29",0603,4,4.7uF,C1705
"C23, C41",1206,2,22uF,C91604
C46,1206,1,22uF,
C47,0603,1,22nF,C106222
C48,0805,1,10uF,
D1,D_SOD-323,1,1N4148WS,C118873
D15,SOT-23,1,BAS70-04,
D2,LED_SK6812MINI_PLCC4_3.5x3.5mm_P1.75mm,1,SK6812MINI,C2886570
"D3, D4, D5, D6",SOT-23,4,BAS70-04,C54194934
D8,D_SOD-323,1,BAT54WS,C124205
F1,1206,1,500mA,C220146
J1,USB_C_Receptacle_HRO_TYPE-C-31-M-12,1,USB_C_Receptacle_USB2.0,C2982555
J2,JST_SH_SM03B-SRSS-TB_1x03-1MP_P1.00mm_Horizontal,1,Conn_01x03_Pin,C160403
"J4, J5, J6, J7",10129382-908003BLF,4,Conn_02x04_Counter_Clockwise,C6970143
L3,L_pol_2016,1,3.3uH,C42411119
L4,1008,1,4.7uH,C668313
"Q10, Q15, Q16, Q17, Q18, Q4, Q6, Q8",SOT-23,8,BSS138,C52895
"Q11, Q12, Q13, Q14, Q3, Q5, Q7, Q9",SOT-23,8,DMG2301L,C7472914
"R10, R11",0603,2,27,C137753
"R100, R101, R110, R111, R112, R113, R130, R133, R134, R138, R140, R143, R145, R148, R150, R153, R155, R158, R63, R64, R74, R77, R82, R85, R90, R93, R98, R99",0603,28,1M,C217860
"R102, R103, R104, R105, R131, R135, R142, R147, R152, R156, R65, R75, R83, R91",0603,14,330,
"R106, R107, R108, R109, R114, R115, R116, R117, R118, R120, R122, R124, R126, R127, R128, R129, R14, R17, R27, R28, R34, R42, R46, R53, R61, R66, R67, R68, R69, R72, R76, R78, R79, R81, R84, R86, R87, R89, R9, R92, R94, R95, R97",0603,43,10K,C98220
"R119, R121, R123, R125, R136, R139, R144, R149, R154, R159, R62, R80, R88, R96",0603,14,120,C125925
R12,0603,1,330R,C105881
"R13, R19, R22, R25",0603,4,300K,
R15,0603,1,33,
"R16, R18, R21, R24",0603,4,820K,
"R2, R4",0603,2,1k,C22548
"R20, R23",0603,2,21.5k,
R26,0603,1,27K,
R29,0603,1,0.5,
"R3, R8",0603,2,5.1k,C105580
"R30, R31, R32, R33",0603,4,100,C125923
"R43, R44, R73",0603,3,0R03,C422943
"R49, R50",0603,2,4k7,C99782
R52,0603,1,300K,C116699
SW1,Panasonic_EVQPUM_EVQPUD,1,SW_Push,C388642
U1,QFN-80-1EP_10x10mm_P0.4mm_EP3.4x3.4mm,1,RP2350_80QFN,
U10,QFN-16_3x3mm_P0.5mm_MPS,1,MP28167-A,
"U11, U4, U8",SOT-23-5,3,INA180A2,C192764
"U13, U14, U19, U20, U21, U22, U23, U24, U26, U28, U30, U31, U32, U33",SOT-23-6,14,SN74LVC1T45DBV,C7843
"U15, U25, U27, U29",SOT-23-6,4,SRV05-4,C558418
"U16, U17, U18",SOT-363_SC-70-6,3,LM66100DCK,C2869734
U2,TSSOP-14_4.4x5mm_P0.65mm,1,TLV9004IPWR,C2058050
U3,WSON-8-1EP_6x5mm_P1.27mm_EP3.4x4.3mm,1,IS25LP064D-JKLA3-TR,C27531352
U5,SOT-666,1,USBLC6-2P6,C2827693
U6,SOT-23-5,1,AP2112K-3.3,C51118
U7,SOT-23,1,LM4040D30IDBZR,C130178
U9,MSOP-8_3x3mm_P0.65mm,1,PI4ULS5V202,C481697
Y1,Crystal_SMD_Abracon_ABM8G-4Pin_3.2x2.5mm,1,ABM8-272-T3,C20625731

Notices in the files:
README.md:
License: GPL-3.0
